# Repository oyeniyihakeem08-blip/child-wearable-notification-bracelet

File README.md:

# Child Wearable Notification Bracelet

A Wi-Fi wristband that lets caregivers in a care facility monitor children and tell each child what is expected of them, such as meal time, bath time or sleep time, wherever they are: caregivers send a clear visual cue with a short message from any browser, the bracelet beeps or buzzes to get the child's attention, and a dashboard tells staff when a bracelet goes offline.

I designed the system architecture, the schematic and the PCB layout, and the caregiver dashboard that goes with it.

> Tools: KiCad, ESP32-S3, MQTT, Next.js · Manufacturing target: JLCPCB

## Highlights

- **Messages on the wrist:** a caregiver picks a child, uploads an image with an optional caption, and it fills the bracelet's 1.69 inch screen with an alert.
- **No app, no pairing:** the bracelet joins the facility's own Wi-Fi and the caregiver uses any phone, tablet or laptop browser, so there is nothing to install.
- **Built-in presence monitoring:** every bracelet checks in regularly, and the dashboard raises an alert showing the child's name, last battery level and last contact time if one goes quiet.
- **Two power strategies:** a 5 minute deep-sleep mode for the longest battery life, or modem sleep for near-instant delivery.
- **Hardware low-battery cutoff:** a nanopower comparator shuts the 3.3 V rail down at about 3.4 V, without depending on firmware.
- **Two independent security layers:** admin-approved caregiver logins on the dashboard, and separate per-bracelet credentials on the MQTT broker with topic-level access control.

## How it works

A message travels from the caregiver's browser to the child's wrist through a cloud relay, so the caregiver does not need to be in the same room or building.

1. The caregiver selects a bracelet on the dashboard, uploads an image with an optional caption and taps Send.
2. The dashboard resizes the image to 240 x 280 px JPEG, uploads it to cloud storage and gets a URL.
3. The dashboard publishes an MQTT message with the image URL, caption and a message ID (QoS 1, retained).
4. The bracelet wakes, or receives it instantly in modem sleep mode, connects to the broker and gets the message.
5. The firmware compares the message ID with the last one stored in flash, and only continues if it is new.
6. The bracelet downloads the JPEG over HTTPS, decodes it to RGB565 and pushes it to the display over SPI.
7. The bracelet alerts the child, and the image stays on screen for 60 seconds before the idle screen (name and time) returns.
8. The bracelet publishes a delivery acknowledgement, and the dashboard shows the message as delivered.
9. The message ID is saved to flash and the bracelet goes back to sleep.

### Setup and reset

On first power-up the bracelet starts its own temporary Wi-Fi network. The caregiver connects to it from any phone or laptop, a setup page opens in the browser, and they enter the facility Wi-Fi details and the child's name. A recessed reset button, only reachable with a pen tip, clears the stored setup so the bracelet can be given to another child.

### Presence and low battery

Every wake cycle the bracelet publishes a status heartbeat. If the broker stops hearing from it, the MQTT Last Will fires and the dashboard raises an alert with the child's name, last battery level and time of last contact, after a grace period that avoids false alarms from a brief router hiccup. When the battery is low, both the bracelet's display and the dashboard tell staff to collect it for charging.

## Hardware

Everything sits inside the bracelet enclosure. The only thing the facility provides is its existing Wi-Fi router.

### Schematic

### PCB renders

| Front | Back |
| --- | --- |
|  |  |

### Display

### Components

| Block | Part | Role |
| --- | --- | --- |
| Microcontroller | ESP32-S3-WROOM-1-N8R8 | Runs the firmware, Wi-Fi, display, sleep and wake cycles. Antenna is integrated in the module. |
| Display | ER-TFT1.69-3, 1.69 inch IPS, 240 x 280, ST7789V | Shows images, name, time and battery status over 4-wire SPI, through an FPC connector. |
| Charger | BQ24074RGT | Charges the LiPo cell from a 5 V input and powers the system, with a charge status line to the MCU. |
| Battery | 400 mAh single-cell LiPo, 3.7 V | Main energy source. |
| 3.3 V regulator | AP2112K-3.3 | Converts the battery voltage to a stable 3.3 V rail. Its enable pin is driven by the low-battery comparator. |
| Fuel gauge | MAX17048G+T10 | Reports battery percentage over I2C, with an alert line to the MCU. |
| Low-battery cutoff | TLV3691IDCKR comparator | Shuts the 3.3 V rail down at low battery and restores it after recharge, with hysteresis. |
| Backlight drive | AO3400A MOSFET + 8.2 ohm resistor | MCU PWM on one pin dims the backlight. |
| Alert | Linear resonant actuator (vibration motor) + AO3400A + 1N4148W | Vibrates on a new message. The diode protects the MOSFET from the motor's flyback. |
| Factory reset | TS-1187A-B-A-B recessed switch | Long press clears setup data and reboots into setup mode. |
| Programming | Tag-Connect TC2030 | Flash and debug without a header on the board. |

### Pin assignments

| Function | GPIO | Net |
| --- | --- | --- |
| Display data (MOSI) | GPIO4 | SDA_Display |
| Display clock | GPIO6 | SCL_Display |
| Display chip select | GPIO7 | CS_Display |
| Display data / command | GPIO8 | RS |
| Display reset | GPIO9 | RESET_Display |
| Charger status input | GPIO5 | CHG_Status |
| Backlight drive | GPIO10 | Backlight |
| Fuel gauge I2C data | GPIO11 | I2C_SDA |
| Fuel gauge I2C clock | GPIO12 | I2C_SCL |
| Fuel gauge alert | GPIO13 | MAX17048_ALERT |
| Vibration motor | GPIO14 | Motor drive |
| Factory reset button | GPIO16 | FACTORY_RESET |
| Boot mode | GPIO0 | BOOT |
| Programming / debug | GPIO43 / GPIO44 | UART_TX / UART_RX |

## Engineering decisions

### Wi-Fi and MQTT instead of Bluetooth

Bluetooth Low Energy would have been the best fit for a small wearable, because its very low power consumption gives the longest battery life. I chose Wi-Fi because range mattered more to me than the extra uptime BLE brings. BLE would need the caregiver's phone or a gateway near the child at all times, while Wi-Fi relies on the facility's existing router, which already exists almost everywhere. That gives whole-building coverage with no new infrastructure, so the bracelet works anywhere a phone gets Wi-Fi. The trade-off is shorter battery life, which is why the design offers a deep-sleep mode.

### The image travels by URL, not through MQTT

MQTT is built for small messages, not image files. The message carries only the image URL and the bracelet downloads the JPEG over HTTPS. That keeps MQTT light and makes the pre-loaded image library possible.

### A display that runs straight from the battery

I rejected a Newhaven 1.5 inch display because its backlight needs a boost converter of up to 14 V, a heavy power-design burden on a battery wearable. The ER-TFT1.69-3 backlight runs directly from the battery.

### Charger set for a small cell

The BQ24074 fast-charge current is set by a 4.7 k resistor on ISET, about 189 mA, close to C/2 for the 400 mAh cell. Pre-charge is set automatically at about 19 mA for a deeply discharged cell. The 3.3 k ILIM resistor and the EN1 high / EN2 low setting follow the datasheet for a 500 mA maximum input.

### Low-battery cutoff in hardware

A TLV3691 nanopower comparator watches the battery through a resistor network with 20 M feedback for hysteresis, and drives the enable pin of the AP2112K regulator. The 3.3 V rail shuts down when the battery falls below about 3.4 V and comes back after recharge. Protection does not depend on firmware, so a firmware crash cannot drain the cell past safe levels.

## Connectivity and firmware

### Communication stack

| Layer | Technology | Purpose |
| --- | --- | --- |
| Physical | Wi-Fi 802.11 b/g/n, 2.4 GHz | Bracelet to the facility router |
| Security | TLS 1.2 on port 8883 | Encrypts all traffic |
| Messaging | MQTT v3.1.1 on HiveMQ Cloud | Lightweight messages, QoS 1 delivery, retained messages, Last Will |
| Image delivery | HTTPS GET | The bracelet fetches the image by URL |
| Setup | Wi-Fi SoftAP + captive portal | One-time setup from any phone or laptop |

### Firmware modules (ESP32-S3)

| Module | Responsibility |
| --- | --- |
| Boot manager | Checks stored setup data and routes to setup mode or normal boot. Detects the factory reset hold. |
| SoftAP provisioning | Runs the temporary access point and captive portal, and stores the Wi-Fi details and device name. |
| Wi-Fi / MQTT manager | Connects to the router and broker, handles retries, TLS, Last Will and status publishing. |
| Wake / sleep manager | Controls the deep-sleep timer or modem sleep mode. One wake cycle handles both the heartbeat and the message check. |
| Image handler | Downloads the JPEG, decodes it to RGB565, renders it, and manages the pre-loaded image slots. |
| Display driver | Initialises the ST7789V over SPI, draws images, text and the idle screen, controls backlight PWM and display sleep. |
| Fuel gauge driver | Reads the battery percentage over I2C and adds it to the status message. |
| NVS manager | Stores Wi-Fi details, device name, the last message ID and the pre-loaded image data. |

### Two power strategies

The design offers two modes, switchable by a firmware update, because different deployments value different things.

| | 5 minute deep sleep | Modem sleep |
| --- | --- | --- |
| How it works | Wakes every 5 minutes, connects, checks for messages, publishes status, sleeps | Stays awake, Wi-Fi radio dozes between router beacons, MQTT connection stays alive |
| Message delivery | Up to 5 minutes | Within seconds |
| Out-of-range detection | Up to 5 minutes | Under 2 minutes |
| Estimated runtime, 1 to 2 messages per hour | about 30 to 33 hours | about 14 to 15 hours |
| Best for | Longest battery life | Instant delivery, daily charging |

### Reliability

- **Wake randomisation:** each bracelet's timer is offset by a random value at setup, so 20 bracelets do not all hit the router at once.
- **QoS 1 and retained messages:** the broker retries unacknowledged messages and holds the latest one until the bracelet reconnects.
- **Wi-Fi retry:** the firmware retries the connection up to 3 times and then shows a no-connection indicator, so it never needs a manual restart.

## Caregiver dashboard

It is a monorepo (Next.js with pnpm workspaces and Turborepo) that keeps each function in its own package, with Supabase (Postgres and Storage) for accounts and images and HiveMQ Cloud as the MQTT broker.

| Devices | Broadcast to a child |
| --- | --- |
|  |  |

### Security

Two independent layers protect the system, so compromising one does not expose the other.

| Layer | How it works |
| --- | --- |
| Dashboard login | Caregivers sign in with email and password and receive a signed JWT. New accounts need administrator approval, and an administrator can revoke access immediately. |
| MQTT broker | Each bracelet has its own client ID, username and password, and the broker's access control list limits each set of credentials to its own topics. |

All connections, from browser to backend, backend to broker and bracelet to broker, use TLS 1.2 on port 8883. A compromised bracelet credential affects only that bracelet.

## Repository layout

```text

├── Child wereable.kicad_pro / .kicad_sch / .kicad_pcb   KiCad project
├── fp-lib-table, sym-lib-table                          Project library tables
├── 3D models/                                           STEP models for the parts
├── Footprint/                                           Custom footprints (.pretty libraries)
├── Symbol/                                              Custom symbols (.kicad_sym)
├── Child wereble Fabrication files/
│   ├── Bom.csv, designators.csv, CPL_positions.csv      Assembly data
│   ├── Child wereable Bill of material.csv              Full bill of materials
│   ├── netlist.ipc                                      IPC netlist
│   ├── Child_wereable.zip                               (Gerbers) 
│   ├── PCB 3D model/                                    Board STEP model
│   └── PDFs/                                            Front/back fab and schematic PDFs
├── Docs/
│   ├── Child Wearable System Architecture.pdf           System architecture document
│   ├── System-architecture-clarifications.pdf           
│   ├── Schematic.pdf                                    Schematic (PDF)
│   ├── Child wereable Schematic.svg                     Schematic (SVG, shown in this README)
│   ├── Front Fab.pdf, Back Fab.pdf                      Front and back fabrication drawings
│   ├── Front of wereable watch.png                      Front PCB render
│   ├── Back of wereable watch .png                      Back PCB render
│   ├── 1.69 inch display.png                            Display photo
│   ├── Devices.jpeg                                     Dashboard: devices page
│   ├── Broadcast child.jpeg                             Dashboard: broadcast page
│   ├── dashboard.png                                    Dashboard screenshot
│   └── Childcare website screnshot.png                  Childcare website screenshot
└── README.md
```

## Author

Hakeem Oyebisi · [oyebisihakeem@gmail.com](mailto:oyebisihakeem@gmail.com) · [GitHub](https://github.com/oyeniyihakeem08-blip)

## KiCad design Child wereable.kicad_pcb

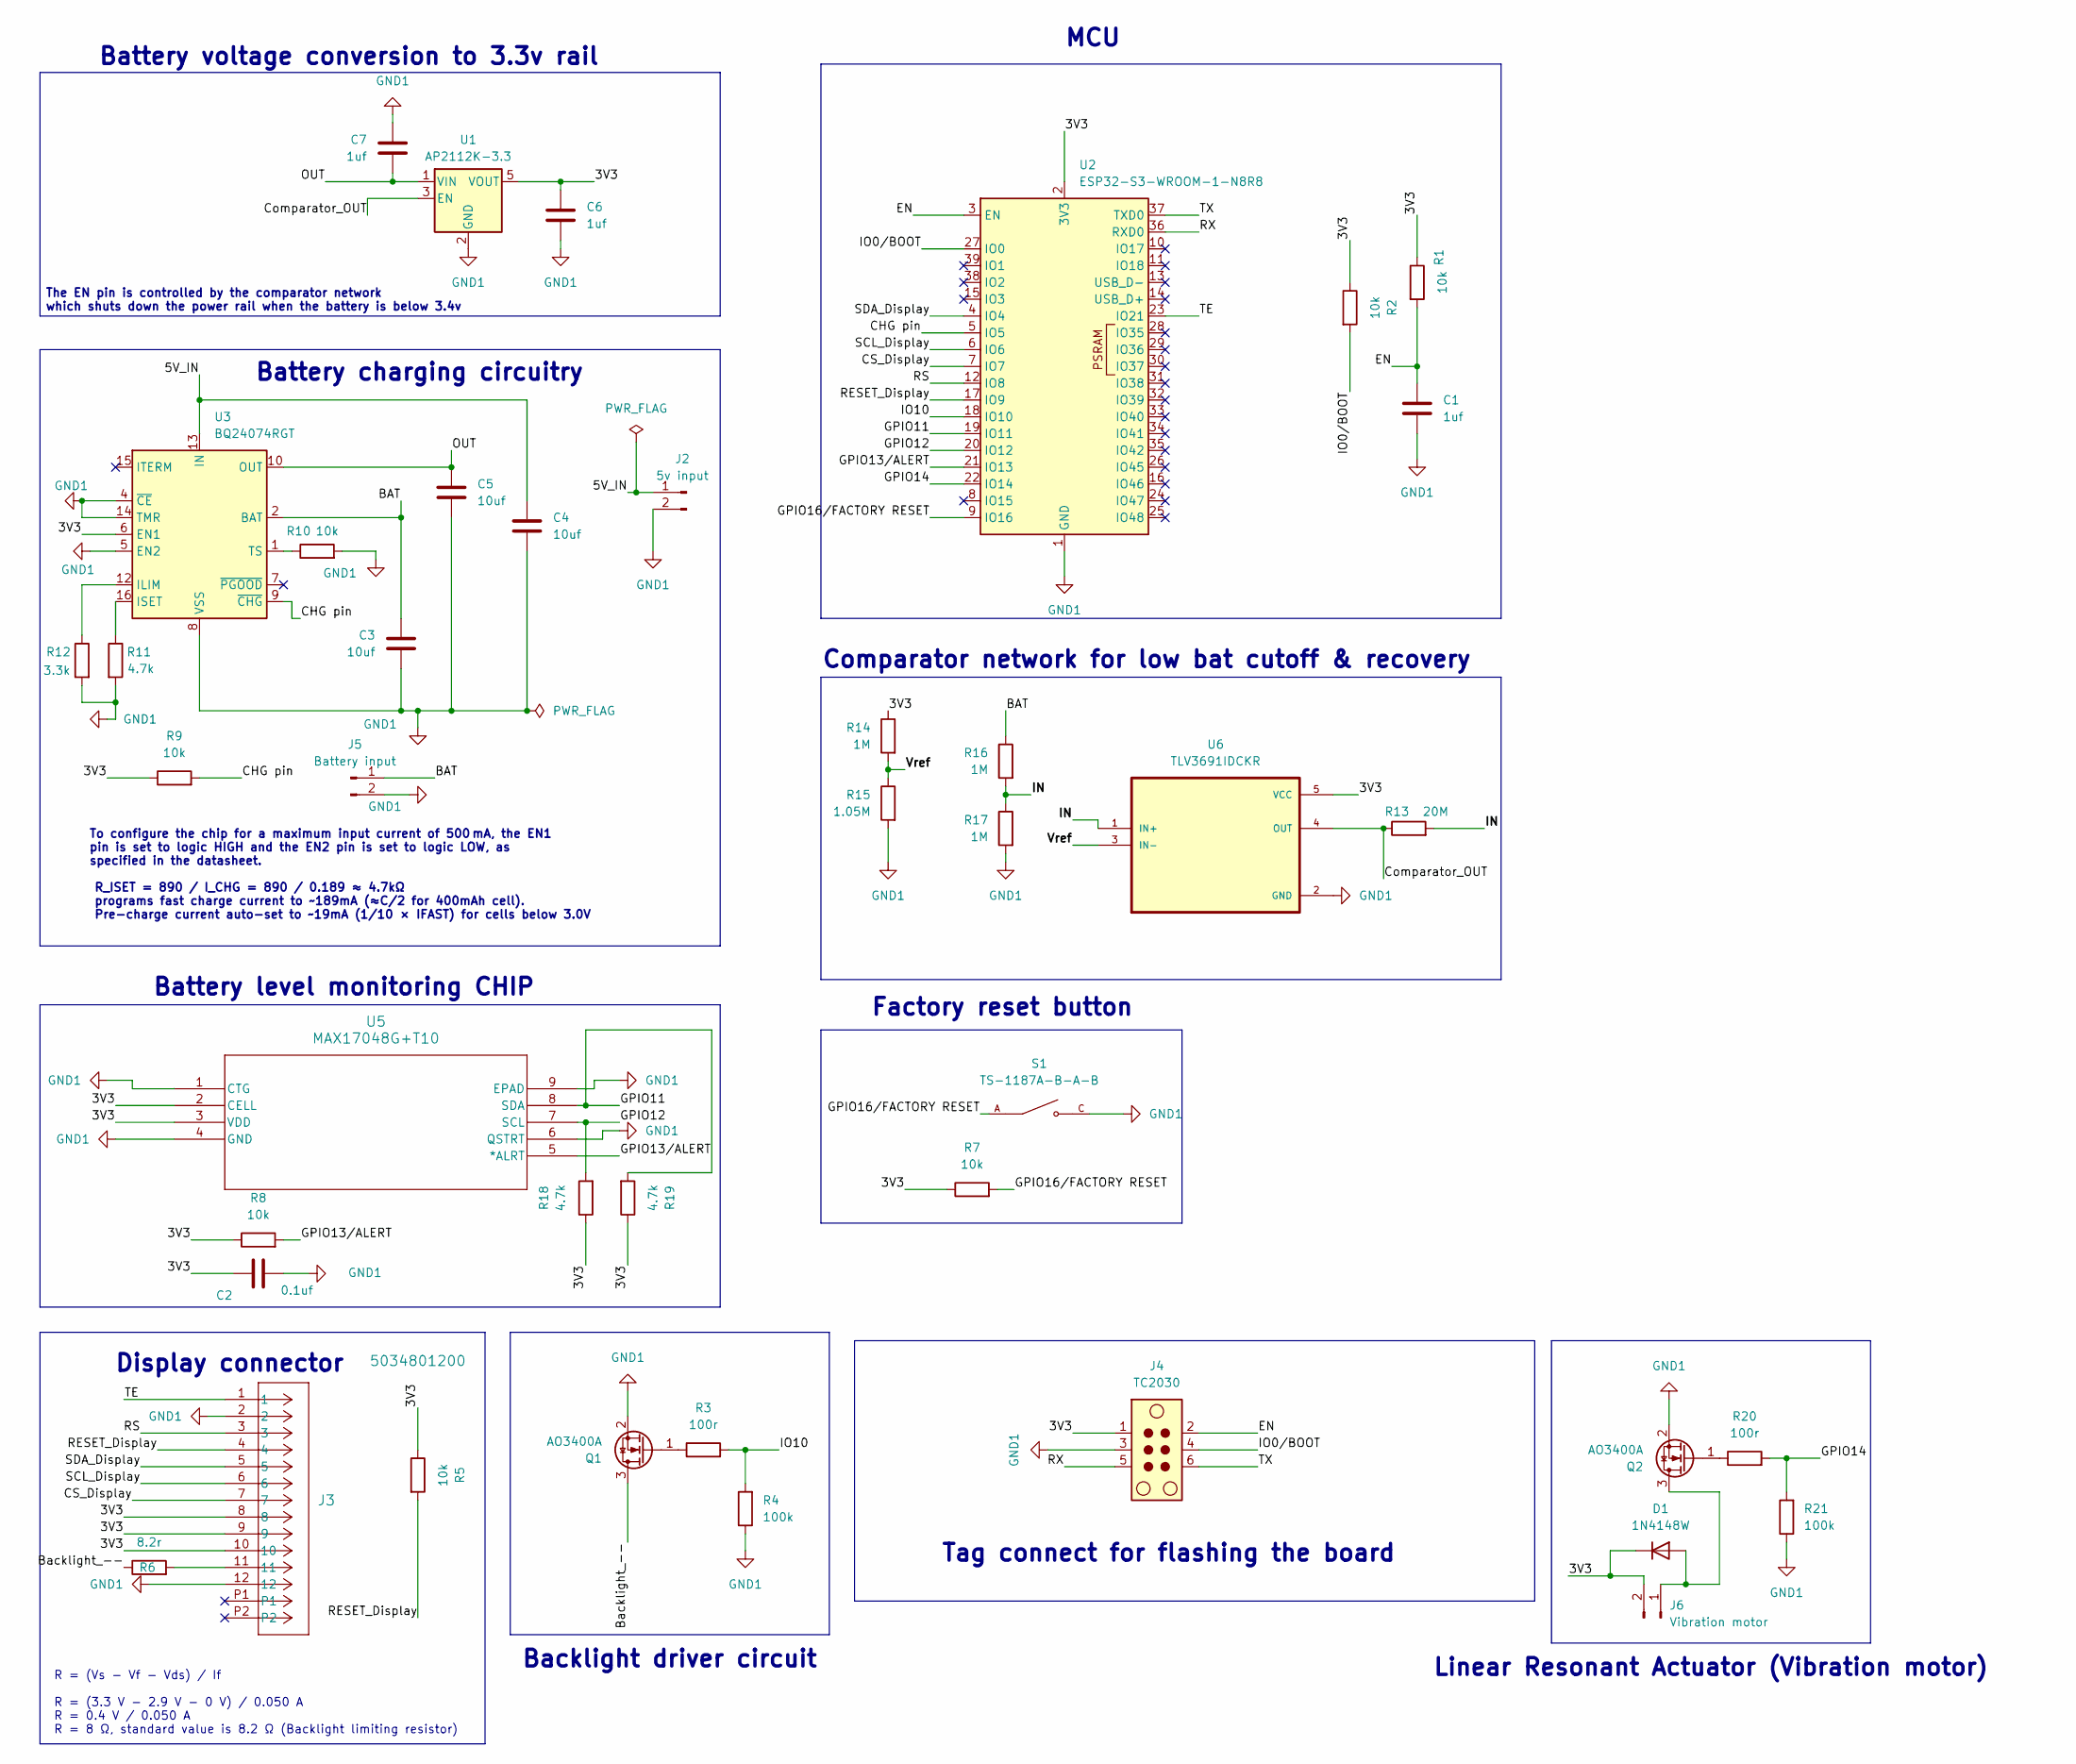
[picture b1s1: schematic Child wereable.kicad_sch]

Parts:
C1, C6, C7: 1uf; C_0603_1608Metric; LCSC PART NO C59782
C2: 0.1uf; C_0603_1608Metric; LCSC PART NO C15725
C3, C4, C5: 10uf; C_0603_1608Metric; LCSC PART NO C19702
D1: 1N4148W; D_SOD-123; LCSC PART NO C81598
J2: 5v input; TestPoint_2Pads_Pitch2.54mm_Drill0.8mm
J3: 5034801200; CON_5034801200_MOL; LCSC PART NO C3169773
J4: TC2030; Tag-Connect_TC2030-IDC-NL_2x03_P1.27mm_Vertical
J5: Battery input; TestPoint_2Pads_Pitch2.54mm_Drill0.8mm
J6: Vibration motor; TestPoint_2Pads_Pitch2.54mm_Drill0.8mm
Q1, Q2: AO3400A; SOT-23; LCSC PART NO C347475
R1, R2, R5, R7, R8, R9, R10: 10k; R_0603_1608Metric; LCSC PART NO C844918
R3, R20: 100r; R_0603_1608Metric; LCSC PART NO C844917
R4, R21: 100k; R_0603_1608Metric; LCSC PART NO C844916
R6: 8.2r; R_0603_1608Metric; LCSC PART NO C2998143
R11, R18, R19: 4.7k; R_0603_1608Metric; LCSC PART NO C844931
R12: 3.3k; R_0603_1608Metric; LCSC PART NO C844928
R13: 20M; R_0603_1608Metric; LCSC PART NO C422963
R14, R16, R17: 1M; R_0603_1608Metric; LCSC PART NO C844922
R15: 1.05M; R_0603_1608Metric; LCSC PART NO C54531148
S1: TS-1187A-B-A-B; SW_TS-1187A-B-A-B; PARTREV A0; LCSC PART NO C318884
U1: AP2112K-3.3; SOT-23-5; LCSC PART NO C51118
U2: ESP32-S3-WROOM-1-N8R8; ESP32-S3-WROOM-1; LCSC PART NO C2913201
U3: BQ24074RGT; VQFN-16-1EP_3x3mm_P0.5mm_EP1.6x1.6mm; LCSC PART NO C54313
U5: MAX17048G+T10; 21-0168E_T822-3_MXM; LCSC PART NO C2682616
U6: TLV3691IDCKR; SOT65P210X110-5N; LCSC PART NO C180352

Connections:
/3V3: C2.1, C6.1, D1.1 (K), J3.8, J3.9, J3.10, J4.1, J6.2, R1.1, R2.1, R5.1, R7.1, R8.1, R9.1, R14.1, R18.1, R19.1, U1.5 (VOUT), U2.2 (3V3), U3.6 (EN1), U5.2 (CELL), U5.3 (VDD), U6.5 (VCC)
/5V_IN: C4.1, J2.1, U3.13 (IN)
/BAT: C3.1, J5.1, R16.1, U3.2 (BAT), U3.3 (BAT)
/Backlight_--: Q1.3 (D), R6.1
/CHG pin: R9.2, U2.5 (IO5), U3.9 (~CHG)
/CS_Display: J3.7, U2.7 (IO7)
/Comparator_OUT: R13.1, U1.3 (EN), U6.4 (OUT)
/EN: C1.1, J4.2, R1.2, U2.3 (EN)
/GPIO11: R19.2, U2.19 (IO11), U5.8 (SDA)
/GPIO12: R18.2, U2.20 (IO12), U5.7 (SCL)
/GPIO13/ALERT: R8.2, U2.21 (IO13), U5.5 (*ALRT)
/GPIO14: R20.2, R21.2, U2.22 (IO14)
/GPIO16/FACTORY RESET: R7.2, S1.A, S1.B, U2.9 (IO16)
/IN: R13.2, R16.2, R17.1, U6.1 (IN+)
/IO0/BOOT: J4.4, R2.2, U2.27 (IO0)
/IO10: R3.2, R4.2, U2.18 (IO10)
/OUT: C5.2, C7.2, U1.1 (VIN), U3.10 (OUT), U3.11 (OUT)
/RESET_Display: J3.4, R5.2, U2.17 (IO9)
/RS: J3.3, U2.12 (IO8)
/RX: J4.5, U2.36 (RXD0)
/SCL_Display: J3.6, U2.6 (IO6)
/SDA_Display: J3.5, U2.4 (IO4)
/TE: J3.1, U2.23 (IO21)
/TX: J4.6, U2.37 (TXD0)
/Vref: R14.2, R15.1, U6.3 (IN-)
GND1: C1.2, C2.2, C3.2, C4.2, C5.1, C6.2, C7.1, J2.2, J3.2, J3.12, J4.3, J5.2, Q1.2 (S), Q2.2 (S), R4.1, R10.2, R11.2, R12.2, R15.2, R17.2, R21.1, S1.C, S1.D, U1.2 (GND), U2.1 (GND), U2.40 (GND), U2.41 (GND), U3.4 (~CE), U3.5 (EN2), U3.8 (VSS), U3.14 (TMR), U3.17 (VSS), U5.1 (CTG), U5.4 (GND), U5.6 (QSTRT), U5.9 (EPAD), U6.2 (GND)
unnamed: D1.2 (A), J6.1, Q2.3 (D)
unnamed: J3.11, R6.2
unnamed: Q1.1 (G), R3.1
unnamed: Q2.1 (G), R20.1
unnamed: R12.1, U3.12 (ILIM)
unnamed: R11.1, U3.16 (ISET)
unnamed: R10.1, U3.1 (TS)

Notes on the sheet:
Factory reset button
Backlight driver circuit
Battery level monitoring CHIP
Battery voltage conversion to 3.3v rail
The EN pin is controlled by the comparator network which shuts down the power rail when the battery is below 3.4v
Display connector
To configure the chip for a maximum input current of 500 mA, the EN1 pin is set to logic HIGH and the EN2 pin is set to logic LOW, as specified in the datasheet.
Comparator network for low bat cutoff & recovery
R = (Vs − Vf − Vds) / If R = (3.3 V − 2.9 V − 0 V) / 0.050 A R = 0.4 V / 0.050 A R = 8 Ω, standard value is 8.2 Ω (Backlight limiting resistor)
Linear Resonant Actuator (Vibration motor)
MCU
R_ISET = 890 / I_CHG = 890 / 0.189 ≈ 4.7kΩ programs fast charge current to ~189mA (≈C/2 for 400mAh cell). Pre-charge current auto-set to ~19mA (1/10 × IFAST) for cells below 3.0V
Tag connect for flashing the board
Battery charging circuitry

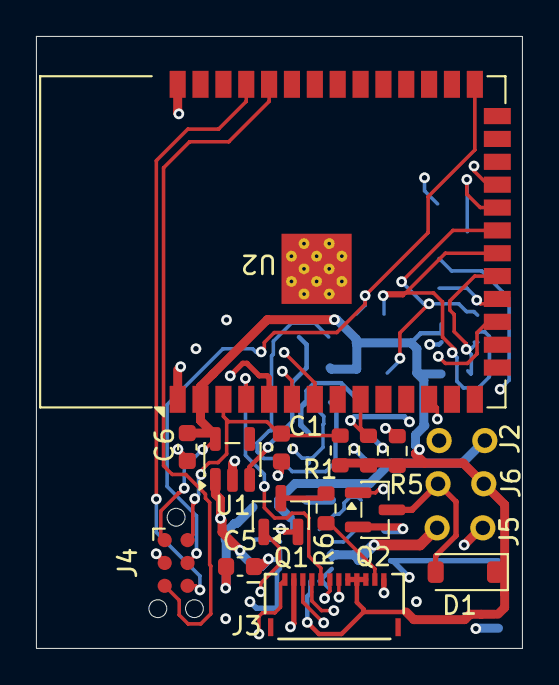
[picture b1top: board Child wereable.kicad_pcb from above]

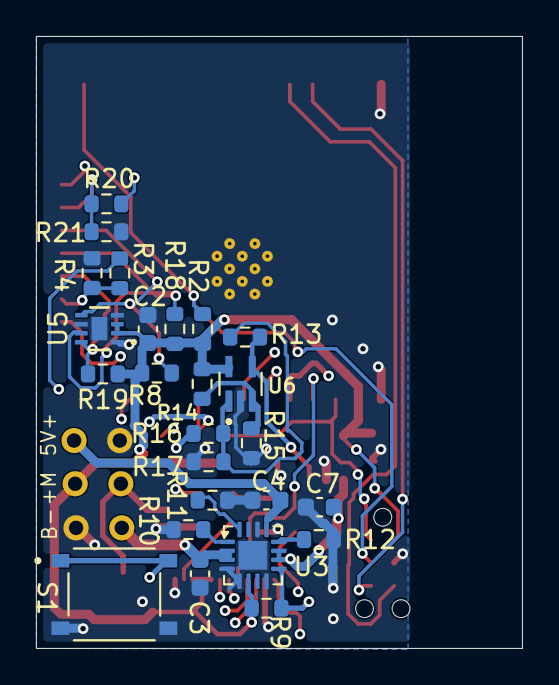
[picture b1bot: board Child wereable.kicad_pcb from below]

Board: 4 copper layers, 27.0 x 34.0 mm, 42 parts (25 on the bottom side), 33 nets.

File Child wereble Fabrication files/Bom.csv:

Designator,Footprint,Quantity,Value,LCSC Part #
"C1, C6, C7",0603,3,1uf,C59782
C2,0603,1,0.1uf,C15725
"C3, C4, C5",0603,3,10uf,C19702
D1,D_SOD-123,1,1N4148W,C81598
J3,CON_5034801200_MOL,1,5034801200,C3169773
"Q1, Q2",SOT-23,2,AO3400A,C347475
"R1, R10, R2, R5, R7, R8, R9",0603,7,10k,C844918
"R11, R18, R19",0603,3,4.7k,C844931
R12,0603,1,3.3k,C844928
R13,0603,1,20M,C422963
"R14, R16, R17",0603,3,1M,C844922
R15,0603,1,1.05M,C54531148
"R20, R3",0603,2,100r,C844917
"R21, R4",0603,2,100k,C844916
R6,0603,1,8.2r,C2998143
S1,SW_TS-1187A-B-A-B,1,TS-1187A-B-A-B,C318884
U1,SOT-23-5,1,AP2112K-3.3,C51118
U2,ESP32-S3-WROOM-1,1,ESP32-S3-WROOM-1-N8R8,C2913201
U3,VQFN-16-1EP_3x3mm_P0.5mm_EP1.6x1.6mm,1,BQ24074RGT,C54313
U5,21-0168E_T822-3_MXM,1,MAX17048G+T10,C2682616
U6,SOT65P210X110-5N,1,TLV3691IDCKR,C180352
